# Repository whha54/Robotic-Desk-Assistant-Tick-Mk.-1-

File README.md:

# Robotic-Desk-Assistant-Tick-Mk.-1-
Everything about my first personal project "Tick Mk. 1"
# Overview
Tick Mk. 1 is designed to be a small desk companion that sits on your workspace while you study. It is programmed to have 4 screens: a face, a Pomodoro timer, a breathing exercise, and a fidget toy. The user can cycle through all 4 of these screens by physically rotating the robot in 90 degree increments. I did this project during my college freshman year summer and learned KiCad, C, and Autodesk Fusion from scratch during that time period. Thank you to Phil's Lab on YouTube for teaching the KiCad basics, Bro Code on YouTube for his excellent C tutorial, and afiskon on GitHub for the SSD1306 STM32 library.
# PCB Design
It is true that this project can successfully be completed on an Arduino or other development boards with much less effort and cost, but I opted for a custom PCB for two reasons. My main reason is that, since this is my first project, I wanted to make a custom PCB so that I can get experience in KiCad and coding in C. My second and more practical reason is that I wanted to make the robot as small as I could, so using an Arduino would significantly increase the total volume the robot occupies. 

For the PCB, I used an STM32F103 microcontroller as STM has an excellent suite of coding applications (STM32CubeMX, STM32CubeIDE, and STM32CubeProgrammer) and ample online resources that allow me to focus on coding only the main logic of the robot instead of spending time doing the low-level configurations. I was initially considering a STM32F411 chip as it had lots of memory and a high execution frequency, but I was able to snag some STM32F103 chips for free at my job over the summer, so I dropped the STM32F411s pretty quickly. To get the STM32 operational, I used a 8MHz external crystal to be stepped up to 72 MHz using the microcontroller's PLL. I also used 2 100K ohm resistors on PA8 as a voltage divider for VBUS sensing. I also set up a pi filter on the VDDA pin to get a super clean power signal. The pi filter is composed of two capacitors and a ferrite bead. As the line travels through the pi filter, high frequency noise is shunted into ground by the first capacitor as higher frequencies result in lower impedances for capacitors. As it travels through the ferrite bead, even more high frequency noise is shaved off as ferrite beads let lower frequencies pass like a near-zero resistance wire but act as a resistive filter to higher frequencies. The second capacitor shunts off even more high frequency noise, and what results is a clean power signal that can be used for the VDDA line.

I wanted the robot to be powered with a battery, so I included a BQ24090DGQ and a USB-C interface for charging. I specifically used the BQ24090DGQ for its easy implementation and clear and thorough datasheet. For the USB-C interface, I also included a USBLC6-2P6 electrostatic discharge (ESD) protection diode array. Since the USB-C port interacts with the real-world frequently, it is possible for there to be a momentary but humongous spike of voltage in an ESD event that may damage the components of the board, so the diode array serves to shunt the massive ESD current safely while clamping the voltage to manageable levels.

Since I want the robot to sense its roll angle, I used the BMI323 IMU. It has options for I3C and SPI communication, but for simplicity, I used the I2C protocol. It also has a tap-detect engine that I used for the fidget toy (the user taps the case to draw circles randomly on the screen). For debugging and code upload, I included Serial Wire Debug (SWD). I also put in mounting holes so that I can use standoffs in the case to mount the PCB. For the screen, I used an 1.3" OLED breakout display I found on Amazon.

For the PCB footprint, I used a 2-layer board for simplicity. It's a relatively standard 2-layer board, but I made sure to use a ground pour on the front and back to simplify wiring. I also put in lots of stitching vias, which serve some pretty cool purposes. Since there are two ground pours, having the stitching vias physically connect the two pours, creating a more unified ground reference. The stitching vias also provide return current a quick way back to the source, which significantly reduces current loop area. Reduced current loop area reduces inductance as it reduces magnetic flux linkage. It also reduces EMI as having the signal and return lines run closer to each other allows some magnetic fields to cancel out, which reduces the amount that radiates outward as EMI.

# Code
I used STM32CubeMX to configure the pins. MX automatically generates the code for the configurations for you and puts in a file, and then you can transfer that file over to CubeIDE to start making your main logic.

The code is pretty basic. I made my own BMI323_Read function as the BMI323 first sends out some dummy bytes before sending real data, so I needed to filter those out myself. I also used software hysteresis to prevent state flickering on the screen. Roll readings are not perfect and flicker just above or just below the true reading, so having two states share the same boundaries (e.g. Pomodoro timer is activated when roll is within 90 degrees to 180 degrees, face is activiated when roll is within 0 degrees to 90 degrees) can cause rapid state changes as the readings fluctuate from just below 90 to just above 90 degrees. I used a complementary filter to get those roll angles. I made sure to fix the wraparound error and also utilized a dynamic alpha so that the readings had less latency. I wrote more information as comments in the code itself.

# CAD of Case
I didn't want to make something super complicated, so I just made a cube with chamfered edges. I hollowed it out and put in some standoffs for the OLED and the PCB so that they can be mounted. I also put in a power switch holder and made a cutout for the USB-C port. I also made it so that it would snap together using a snap case and lid.

# Future Improvements
-4 layer board to make the PCB smaller
-RF design for WiFi/BT so I can put in assignment trackers (increase the functionality of the robot)
-Put in a buzzer that goes off when the Pomodoro timer goes off
-More eye animations

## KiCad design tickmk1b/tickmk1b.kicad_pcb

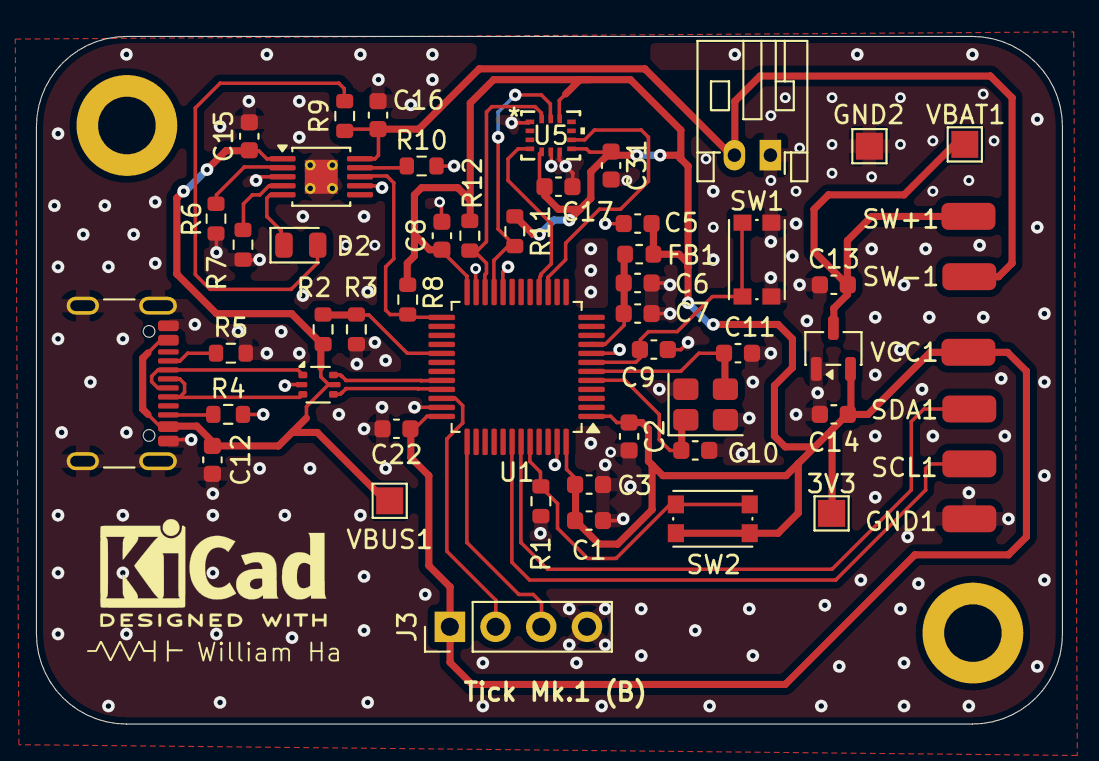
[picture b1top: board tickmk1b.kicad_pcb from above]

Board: 2 copper layers, 57.0 x 38.2 mm, 55 parts (0 on the bottom side), 31 nets.

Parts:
3V3: 3V3; TestPoint_Pad_1.5x1.5mm
C1: 10uF; C_0603_1608Metric
C2, C3, C8, C9, C17, C22, C31: 0.1uF; C_0603_1608Metric
C5, C6, C13, C14, C15, C16: 1uF; C_0603_1608Metric
C7: 10nF; C_0603_1608Metric
C10, C11: 15pF; C_0603_1608Metric
C12: 4.7uF; C_0603_1608Metric
D2: LED; LED_0805_2012Metric
FB1: 600R, 100 MHz; L_0603_1608Metric
GND1: Conn_01x01_Pin; SolderWirePad_1x01_SMD_1.5x3mm
GND2: GND; TestPoint_Pad_1.5x1.5mm
H1, H2: MountingHole; MountingHole_3.2mm_M3_DIN965_Pad
J1: USB_C_Receptacle_USB2.0_16P; USB_C_Receptacle_GCT_USB4105-xx-A_16P_TopMnt_Horizontal
J2: 3V7; JST_PH_S2B-PH-K_02x2.00mm_Angled
J3: SWD; PinHeader_1x04_P2.54mm_Vertical
R1, R8, R10, R11, R12: 10k; R_0603_1608Metric
R2, R3: 100k; R_0603_1608Metric
R4, R5: 5.1k; R_0603_1608Metric
R6: 1k; R_0603_1608Metric
R7: 2k; R_0603_1608Metric
R9: 1k5; R_0603_1608Metric
SCL1: Conn_01x01_Pin; SolderWirePad_1x01_SMD_1.5x3mm
SDA1: Conn_01x01_Pin; SolderWirePad_1x01_SMD_1.5x3mm
SW1: NRST; SW_Push_1P1T_NO_CK_KMR2
SW2: BOOT0; SW_Push_1P1T_NO_CK_KMR2
SW+1: SWOUT; SolderWirePad_1x01_SMD_1.5x3mm
SW-1: SWMID; SolderWirePad_1x01_SMD_1.5x3mm
U1: STM32F103C6Tx; LQFP-48_7x7mm_P0.5mm
U2: BQ24090DGQ; HVSSOP-10-1EP_3x3mm_P0.5mm_EP1.83x1.89mm_ThermalVias
U3: MCP1700x-330xxTT; SOT-23-3
U4: USBLC6-2P6; SOT-666
U5: BMI323; BMI323_BOS
VBAT1: VBAT; TestPoint_Pad_1.5x1.5mm
VBUS1: VBUS; TestPoint_Pad_1.5x1.5mm
VCC1: Conn_01x01_Pin; SolderWirePad_1x01_SMD_1.5x3mm
Y1: 8MHz; Crystal_SMD_3225-4Pin_3.2x2.5mm

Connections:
+3.3VA: C6.1, C7.1, FB1.1, U1.9 (VDDA)
+3V3: 3V3.1 (1_1), C1.1, C2.1, C3.1, C5.1, C8.1, C14.2, C17.1, C22.1, C31.1, FB1.2, J3.1, R8.1, R11.1, R12.1, U1.1 (VBAT), U1.24 (VDD), U1.36 (VDD), U1.44 (BOOT0), U1.48 (VDD), U3.2 (VO), U5.5 (VDDIO), U5.8 (VDD), U5.12 (CSB), VCC1.1 (Pin_1_1)
/CC1: J1.A5 (CC1), R5.1
/CC2: J1.B5 (CC2), R4.1
/CHG: R8.2, U1.25 (PB12), U2.8 (~CHG)
/D+: U1.33 (PA12), U4.4 (I/O2)
/D-: U1.32 (PA11), U4.6 (I/O1)
/DSCL: SCL1.1 (Pin_1_1), U1.42 (PB6)
/DSDA: SDA1.1 (Pin_1_1), U1.43 (PB7)
/INT1: U1.16 (PA6), U5.4 (INT1)
/INT2: U1.15 (PA5), U5.9 (INT2)
/SCL: R11.2, U1.21 (PB10), U5.13 (SCX)
/SDA: R12.2, U1.22 (PB11), U5.14 (SDX)
/SWCLK: J3.3, U1.37 (PA14)
/SWDIO: J3.2, U1.34 (PA13)
GND: C1.2, C2.2, C3.2, C5.2, C6.2, C7.2, C8.2, C9.2, C10.1, C11.1, C12.1, C13.1, C14.1, C15.2, C16.2, C17.2, C22.2, C31.2, GND1.1 (Pin_1_1), GND2.1 (1_1), J1.A1 (GND), J1.A12 (GND), J1.B1 (GND), J1.B12 (GND), J1.SH (SHIELD), J2.1, J3.4, R1.2, R3.2, R4.2, R5.2, R6.2, R7.2, R10.2, SW1.1, U1.8 (VSSA), U1.20 (PB2), U1.23 (VSS), U1.35 (VSS), U1.47 (VSS), U2.3 (VSS), U2.7 (ISET2), U2.11 (VSS), U3.1 (GND), U4.2 (GND), U5.1 (SDO), U5.6 (GNDIO), U5.7 (GND), Y1.2 (G), Y1.4 (G)
unnamed: D2.2 (A), R9.2
unnamed: D2.1 (K), U2.5 (~PG)
unnamed: J1.A6 (D+), J1.B6 (D+), U4.3 (I/O2)
unnamed: J1.A7 (D-), J1.B7 (D-), U4.1 (I/O1)
unnamed: C16.1, J2.2, R9.1, SW-1.1 (Pin_1_1), U2.10 (OUT)
unnamed: R1.1, SW2.1
unnamed: C9.1, SW1.2, U1.7 (NRST)
unnamed: R2.2, R3.1, U1.29 (PA8)
unnamed: C10.2, U1.5 (PD0), Y1.1
unnamed: C11.2, U1.6 (PD1), Y1.3
unnamed: R6.1, U2.2 (ISET)
unnamed: R7.1, U2.4 (PRETERM)
unnamed: R10.1, U2.9 (TS)
VBAT: C13.2, SW+1.1 (Pin_1_1), U3.3 (VI), VBAT1.1 (1_1)
VBUS: C12.2, C15.1, J1.A4 (VBUS), J1.A9 (VBUS), J1.B4 (VBUS), J1.B9 (VBUS), R2.1, U2.1 (IN), U4.5 (VBUS), VBUS1.1 (1_1)

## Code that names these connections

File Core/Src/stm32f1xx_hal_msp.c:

/* USER CODE BEGIN Header */
/**
  ******************************************************************************
  * @file         stm32f1xx_hal_msp.c
  * @brief        This file provides code for the MSP Initialization
  *               and de-Initialization codes.
  ******************************************************************************
  * @attention
  *
  * Copyright (c) 2026 STMicroelectronics.
  * All rights reserved.
  *
  * This software is licensed under terms that can be found in the LICENSE file
  * in the root directory of this software component.
  * If no LICENSE file comes with this software, it is provided AS-IS.
  *
  ******************************************************************************
  */
/* USER CODE END Header */
/* Includes ------------------------------------------------------------------*/
#include "main.h"
/* USER CODE BEGIN Includes */

/* USER CODE END Includes */

/* Private typedef -----------------------------------------------------------*/
/* USER CODE BEGIN TD */

/* USER CODE END TD */

/* Private define ------------------------------------------------------------*/
/* USER CODE BEGIN Define */

/* USER CODE END Define */

/* Private macro -------------------------------------------------------------*/
/* USER CODE BEGIN Macro */

/* USER CODE END Macro */

/* Private variables ---------------------------------------------------------*/
/* USER CODE BEGIN PV */

/* USER CODE END PV */

/* Private function prototypes -----------------------------------------------*/
/* USER CODE BEGIN PFP */

/* USER CODE END PFP */

/* External functions --------------------------------------------------------*/
/* USER CODE BEGIN ExternalFunctions */

/* USER CODE END ExternalFunctions */

/* USER CODE BEGIN 0 */

/* USER CODE END 0 */
/**
  * Initializes the Global MSP.
  */
void HAL_MspInit(void)
{

  /* USER CODE BEGIN MspInit 0 */

  /* USER CODE END MspInit 0 */

  __HAL_RCC_AFIO_CLK_ENABLE();
  __HAL_RCC_PWR_CLK_ENABLE();

  /* System interrupt init*/

  /** NOJTAG: JTAG-DP Disabled and SW-DP Enabled
  */
  __HAL_AFIO_REMAP_SWJ_NOJTAG();

  /* USER CODE BEGIN MspInit 1 */

  /* USER CODE END MspInit 1 */
}

/**
  * @brief I2C MSP Initialization
  * This function configures the hardware resources used in this example
  * @param hi2c: I2C handle pointer
  * @retval None
  */
void HAL_I2C_MspInit(I2C_HandleTypeDef* hi2c)
{
  GPIO_InitTypeDef GPIO_InitStruct = {0};
  if(hi2c->Instance==I2C1)
  {
    /* USER CODE BEGIN I2C1_MspInit 0 */

    /* USER CODE END I2C1_MspInit 0 */

    __HAL_RCC_GPIOB_CLK_ENABLE();
    /**I2C1 GPIO Configuration
    PB6     ------> I2C1_SCL
    PB7     ------> I2C1_SDA
    */
    GPIO_InitStruct.Pin = DSCL_Pin|DSDA_Pin;
    GPIO_InitStruct.Mode = GPIO_MODE_AF_OD;
    GPIO_InitStruct.Speed = GPIO_SPEED_FREQ_HIGH;
    HAL_GPIO_Init(GPIOB, &GPIO_InitStruct);

    /* Peripheral clock enable */
    __HAL_RCC_I2C1_CLK_ENABLE();
    /* USER CODE BEGIN I2C1_MspInit 1 */

    /* USER CODE END I2C1_MspInit 1 */
  }
  else if(hi2c->Instance==I2C2)
  {
    /* USER CODE BEGIN I2C2_MspInit 0 */

    /* USER CODE END I2C2_MspInit 0 */

    __HAL_RCC_GPIOB_CLK_ENABLE();
    /**I2C2 GPIO Configuration
    PB10     ------> I2C2_SCL
    PB11     ------> I2C2_SDA
    */
    GPIO_InitStruct.Pin = SCL_Pin|SDA_Pin;
    GPIO_InitStruct.Mode = GPIO_MODE_AF_OD;
    GPIO_InitStruct.Speed = GPIO_SPEED_FREQ_HIGH;
    HAL_GPIO_Init(GPIOB, &GPIO_InitStruct);

    /* Peripheral clock enable */
    __HAL_RCC_I2C2_CLK_ENABLE();
    /* USER CODE BEGIN I2C2_MspInit 1 */

    /* USER CODE END I2C2_MspInit 1 */
  }

}

/**
  * @brief I2C MSP De-Initialization
  * This function freeze the hardware resources used in this example
  * @param hi2c: I2C handle pointer
  * @retval None
  */
void HAL_I2C_MspDeInit(I2C_HandleTypeDef* hi2c)
{
  if(hi2c->Instance==I2C1)
  {
    /* USER CODE BEGIN I2C1_MspDeInit 0 */

    /* USER CODE END I2C1_MspDeInit 0 */
    /* Peripheral clock disable */
    __HAL_RCC_I2C1_CLK_DISABLE();

    /**I2C1 GPIO Configuration
    PB6     ------> I2C1_SCL
    PB7     ------> I2C1_SDA
    */
    HAL_GPIO_DeInit(DSCL_GPIO_Port, DSCL_Pin);

    HAL_GPIO_DeInit(DSDA_GPIO_Port, DSDA_Pin);

    /* USER CODE BEGIN I2C1_MspDeInit 1 */

    /* USER CODE END I2C1_MspDeInit 1 */
  }
  else if(hi2c->Instance==I2C2)
  {
    /* USER CODE BEGIN I2C2_MspDeInit 0 */

    /* USER CODE END I2C2_MspDeInit 0 */
    /* Peripheral clock disable */
    __HAL_RCC_I2C2_CLK_DISABLE();

    /**I2C2 GPIO Configuration
    PB10     ------> I2C2_SCL
    PB11     ------> I2C2_SDA
    */
    HAL_GPIO_DeInit(SCL_GPIO_Port, SCL_Pin);

    HAL_GPIO_DeInit(SDA_GPIO_Port, SDA_Pin);

    /* USER CODE BEGIN I2C2_MspDeInit 1 */

    /* USER CODE END I2C2_MspDeInit 1 */
  }

}

/**
  * @brief TIM_Base MSP Initialization
  * This function configures the hardware resources used in this example
  * @param htim_base: TIM_Base handle pointer
  * @retval None
  */
void HAL_TIM_Base_MspInit(TIM_HandleTypeDef* htim_base)
{
  if(htim_base->Instance==TIM2)
  {
    /* USER CODE BEGIN TIM2_MspInit 0 */

    /* USER CODE END TIM2_MspInit 0 */
    /* Peripheral clock enable */
    __HAL_RCC_TIM2_CLK_ENABLE();
    /* TIM2 interrupt Init */
    HAL_NVIC_SetPriority(TIM2_IRQn, 0, 0);
    HAL_NVIC_EnableIRQ(TIM2_IRQn);
    /* USER CODE BEGIN TIM2_MspInit 1 */

    /* USER CODE END TIM2_MspInit 1 */

  }

}

/**
  * @brief TIM_Base MSP De-Initialization
  * This function freeze the hardware resources used in this example
  * @param htim_base: TIM_Base handle pointer
  * @retval None
  */
void HAL_TIM_Base_MspDeInit(TIM_HandleTypeDef* htim_base)
{
  if(htim_base->Instance==TIM2)
  {
    /* USER CODE BEGIN TIM2_MspDeInit 0 */

    /* USER CODE END TIM2_MspDeInit 0 */
    /* Peripheral clock disable */
    __HAL_RCC_TIM2_CLK_DISABLE();

    /* TIM2 interrupt DeInit */
    HAL_NVIC_DisableIRQ(TIM2_IRQn);
    /* USER CODE BEGIN TIM2_MspDeInit 1 */

    /* USER CODE END TIM2_MspDeInit 1 */
  }

}

/* USER CODE BEGIN 1 */

/* USER CODE END 1 */

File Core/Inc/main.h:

/* USER CODE BEGIN Header */
/**
  ******************************************************************************
  * @file           : main.h
  * @brief          : Header for main.c file.
  *                   This file contains the common defines of the application.
  ******************************************************************************
  * @attention
  *
  * Copyright (c) 2026 STMicroelectronics.
  * All rights reserved.
  *
  * This software is licensed under terms that can be found in the LICENSE file
  * in the root directory of this software component.
  * If no LICENSE file comes with this software, it is provided AS-IS.
  *
  ******************************************************************************
  */
/* USER CODE END Header */

/* Define to prevent recursive inclusion -------------------------------------*/
#ifndef __MAIN_H
#define __MAIN_H

#ifdef __cplusplus
extern "C" {
#endif

/* Includes ------------------------------------------------------------------*/
#include "stm32f1xx_hal.h"

/* Private includes ----------------------------------------------------------*/
/* USER CODE BEGIN Includes */

/* USER CODE END Includes */

/* Exported types ------------------------------------------------------------*/
/* USER CODE BEGIN ET */

/* USER CODE END ET */

/* Exported constants --------------------------------------------------------*/
/* USER CODE BEGIN EC */

/* USER CODE END EC */

/* Exported macro ------------------------------------------------------------*/
/* USER CODE BEGIN EM */

/* USER CODE END EM */

/* Exported functions prototypes ---------------------------------------------*/
void Error_Handler(void);

/* USER CODE BEGIN EFP */

/* USER CODE END EFP */

/* Private defines -----------------------------------------------------------*/
#define INT2_Pin GPIO_PIN_5
#define INT2_GPIO_Port GPIOA
#define INT2_EXTI_IRQn EXTI9_5_IRQn
#define INT1_Pin GPIO_PIN_6
#define INT1_GPIO_Port GPIOA
#define INT1_EXTI_IRQn EXTI9_5_IRQn
#define SCL_Pin GPIO_PIN_10
#define SCL_GPIO_Port GPIOB
#define SDA_Pin GPIO_PIN_11
#define SDA_GPIO_Port GPIOB
#define CHG_Pin GPIO_PIN_12
#define CHG_GPIO_Port GPIOB
#define VBUS_SENSE_Pin GPIO_PIN_8
#define VBUS_SENSE_GPIO_Port GPIOA
#define VBUS_SENSE_EXTI_IRQn EXTI9_5_IRQn
#define D__Pin GPIO_PIN_11
#define D__GPIO_Port GPIOA
#define D_A12_Pin GPIO_PIN_12
#define D_A12_GPIO_Port GPIOA
#define SWDIO_Pin GPIO_PIN_13
#define SWDIO_GPIO_Port GPIOA
#define SWCLK_Pin GPIO_PIN_14
#define SWCLK_GPIO_Port GPIOA
#define DSCL_Pin GPIO_PIN_6
#define DSCL_GPIO_Port GPIOB
#define DSDA_Pin GPIO_PIN_7
#define DSDA_GPIO_Port GPIOB

/* USER CODE BEGIN Private defines */

/* USER CODE END Private defines */

#ifdef __cplusplus
}
#endif

#endif /* __MAIN_H */
